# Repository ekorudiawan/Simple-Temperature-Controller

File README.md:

# Simple-Temperature-Controller
Simple Temperature Controller

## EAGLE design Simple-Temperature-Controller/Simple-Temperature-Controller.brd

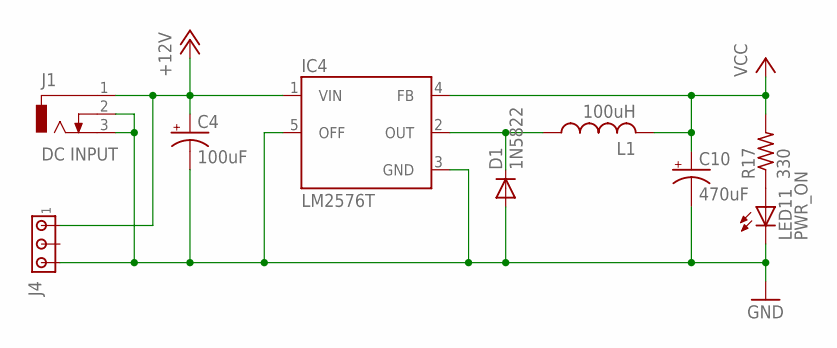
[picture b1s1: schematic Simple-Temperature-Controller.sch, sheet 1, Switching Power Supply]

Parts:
C4: 100uF; E2,5-6
C10: 470uF; E3,5-8
D1: 1N5822; DO201-15
IC4: LM2576T; TO220-5
J1: DC INPUT; DCJ0202
J4: MTA03-100; 10X03MTA
L1: 100uH; TJ3-U2
LED11: PWR_ON; LED3MM
R17: 330; 0207/10

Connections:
+12V: C4.+, IC4.1 (VIN), J1.1, J4.1; also elsewhere on the board
GND: C4.-, C10.-, D1.A, IC4.3 (GND), IC4.5 (OFF), J1.2, J1.3, J4.3, LED11.K (C); also elsewhere on the board
unnamed: D1.C, IC4.2 (OUT), L1.1
unnamed: LED11.A, R17.1
VCC: C10.+, IC4.4 (FB), L1.2, R17.2; also elsewhere on the board

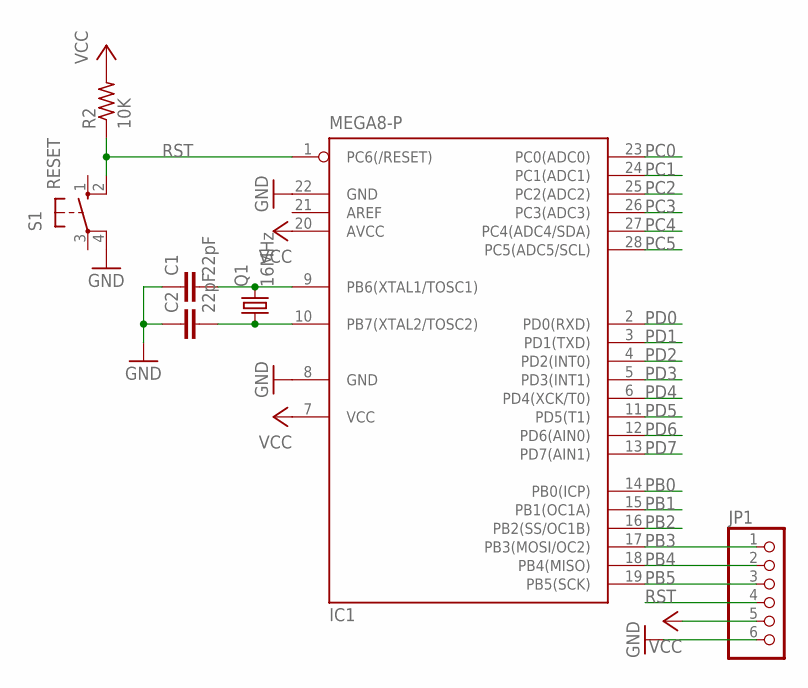
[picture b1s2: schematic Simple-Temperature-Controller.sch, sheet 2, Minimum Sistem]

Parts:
C1, C2: 22pF; RESISTOR_C025-024X044
IC1: MEGA8-P; DIL28-3
JP1: PINHD-1X6; 1X06
Q1: 16MHz; HC49/S
R2: 10K; RESISTOR_0207/10
S1: RESET; B3F-10XX

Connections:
GND: C1.1, C2.1, IC1.8 (GND), IC1.22 (GND), JP1.6, S1.4 (P1); also elsewhere on the board
unnamed: C1.2, IC1.9 (PB6(XTAL1/TOSC1)), Q1.2
unnamed: C2.2, IC1.10 (PB7(XTAL2/TOSC2)), Q1.1
PB0: IC1.14 (PB0(ICP)); also elsewhere on the board
PB1: IC1.15 (PB1(OC1A)); also elsewhere on the board
PB2: IC1.16 (PB2(SS/OC1B)); also elsewhere on the board
PB3: IC1.17 (PB3(MOSI/OC2)), JP1.1; also elsewhere on the board
PB4: IC1.18 (PB4(MISO)), JP1.2; also elsewhere on the board
PB5: IC1.19 (PB5(SCK)), JP1.3; also elsewhere on the board
PC0: IC1.23 (PC0(ADC0)); also elsewhere on the board
PC1: IC1.24 (PC1(ADC1)); also elsewhere on the board
PC2: IC1.25 (PC2(ADC2)); also elsewhere on the board
PC3: IC1.26 (PC3(ADC3)); also elsewhere on the board
PC4: IC1.27 (PC4(ADC4/SDA)); also elsewhere on the board
PC5: IC1.28 (PC5(ADC5/SCL)); also elsewhere on the board
PD0: IC1.2 (PD0(RXD)); also elsewhere on the board
PD1: IC1.3 (PD1(TXD)); also elsewhere on the board
PD2: IC1.4 (PD2(INT0)); also elsewhere on the board
PD3: IC1.5 (PD3(INT1)); also elsewhere on the board
PD4: IC1.6 (PD4(XCK/T0)); also elsewhere on the board
PD5: IC1.11 (PD5(T1))
PD6: IC1.12 (PD6(AIN0))
PD7: IC1.13 (PD7(AIN1))
RST: IC1.1 (PC6(/RESET)), JP1.4, R2.1, S1.2 (S1)
VCC: IC1.7 (VCC), IC1.20 (AVCC), JP1.5, R2.2; also elsewhere on the board

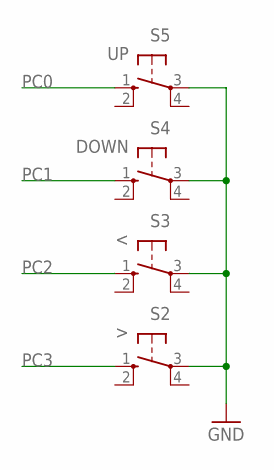
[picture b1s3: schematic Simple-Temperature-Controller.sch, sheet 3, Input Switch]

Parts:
S2: >; B3F-10XX; MPN B3F-1000
S3: <; B3F-10XX; MPN B3F-1000
S4: DOWN; B3F-10XX; MPN B3F-1000
S5: UP; B3F-10XX; MPN B3F-1000

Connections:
GND: S2.3, S3.3, S4.3, S5.3; also elsewhere on the board
PC0: S5.1 (S); also elsewhere on the board
PC1: S4.1 (S); also elsewhere on the board
PC2: S3.1 (S); also elsewhere on the board
PC3: S2.1 (S); also elsewhere on the board

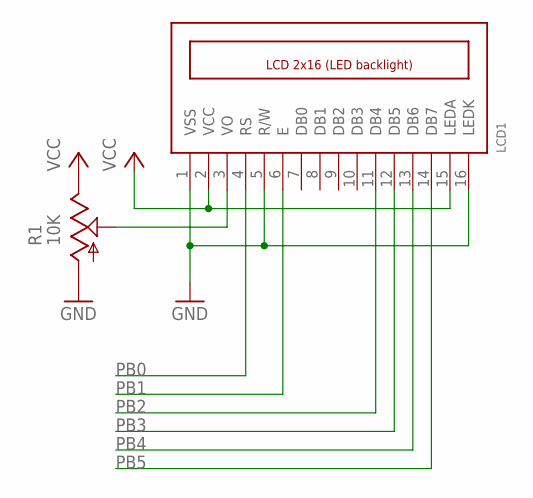
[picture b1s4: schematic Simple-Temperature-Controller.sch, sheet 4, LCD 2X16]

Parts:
LCD1: LCD-2X16
R1: 10K; POT_CA6V

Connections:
GND: LCD1.1 (VSS), LCD1.5 (R/W), LCD1.16 (LEDK), R1.A; also elsewhere on the board
unnamed: LCD1.3 (VO), R1.S
PB0: LCD1.4 (RS); also elsewhere on the board
PB1: LCD1.6 (E); also elsewhere on the board
PB2: LCD1.11 (DB4); also elsewhere on the board
PB3: LCD1.12 (DB5); also elsewhere on the board
PB4: LCD1.13 (DB6); also elsewhere on the board
PB5: LCD1.14 (DB7); also elsewhere on the board
VCC: LCD1.2 (VCC), LCD1.15 (LEDA), R1.E; also elsewhere on the board

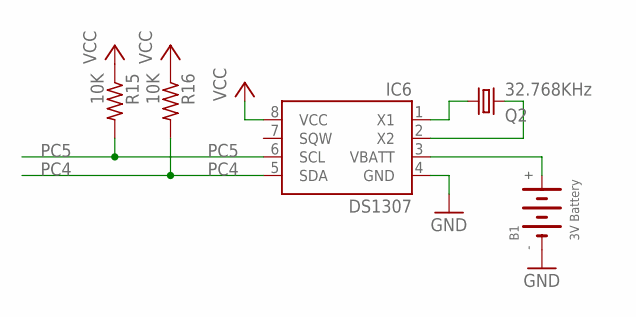
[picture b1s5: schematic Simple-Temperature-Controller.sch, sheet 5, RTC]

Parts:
B1: 3V Battery; CR2032
IC6: DS1307; DIP08
Q2: 32.768KHz; TC26H
R15, R16: 10K; 0207/10

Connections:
GND: B1.-, IC6.4 (GND); also elsewhere on the board
unnamed: IC6.1 (X1), Q2.1
unnamed: IC6.2 (X2), Q2.2
unnamed: B1.+, IC6.3 (VBATT)
PC4: IC6.5 (SDA), R16.2; also elsewhere on the board
PC5: IC6.6 (SCL), R15.2; also elsewhere on the board
VCC: IC6.8 (VCC), R15.1, R16.1; also elsewhere on the board

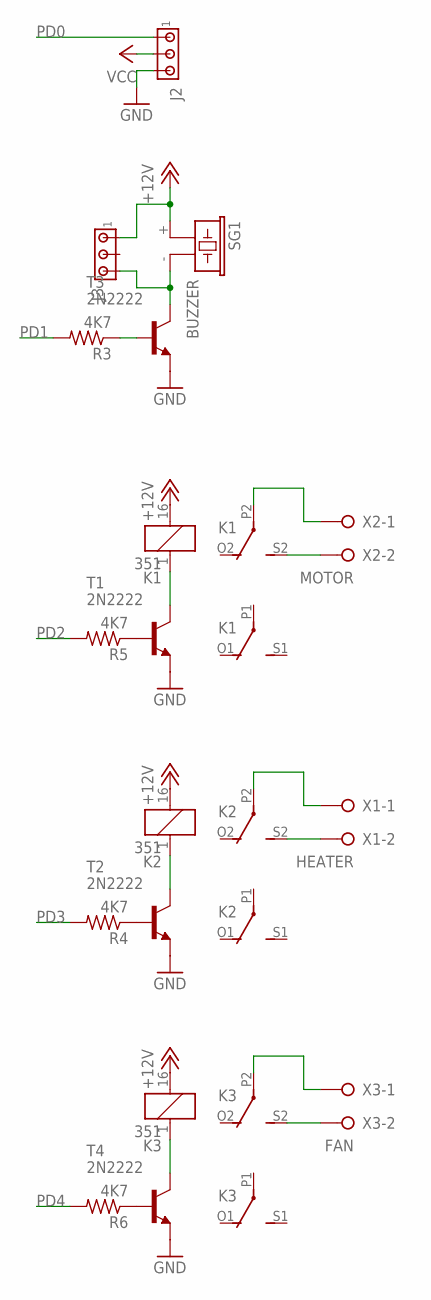
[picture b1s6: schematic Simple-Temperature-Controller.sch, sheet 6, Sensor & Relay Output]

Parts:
J2, J3: MTA03-100; 10X03MTA
K1, K2, K3: 351
R3, R4, R5, R6: 4K7; 0207/10
SG1: BUZZER; F/CM12P
T1, T2, T3, T4: 2N2222; TO92-EBC-OVAL
X1: HEATER; W237-132
X2: MOTOR; W237-132
X3: FAN; W237-132

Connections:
+12V: J3.1, K1.16 (2), K2.16 (2), K3.16 (2), SG1.+ (1); also elsewhere on the board
GND: J2.3, T1.E, T2.E, T3.E, T4.E; also elsewhere on the board
unnamed: R5.1, T1.B
unnamed: K1.1, T1.C
unnamed: K2.1, T2.C
unnamed: K1.P2, X2.1
unnamed: K2.S2 (S), X1.2
unnamed: R4.1, T2.B
unnamed: K3.1, T4.C
unnamed: K3.S2 (S), X3.2
unnamed: R6.1, T4.B
unnamed: K1.S2 (S), X2.2
unnamed: K2.P2, X1.1
unnamed: K3.P2, X3.1
unnamed: J3.3, SG1.- (2), T3.C
unnamed: R3.1, T3.B
PD0: J2.1; also elsewhere on the board
PD1: R3.2; also elsewhere on the board
PD2: R5.2; also elsewhere on the board
PD3: R4.2; also elsewhere on the board
PD4: R6.2; also elsewhere on the board
VCC: J2.2; also elsewhere on the board

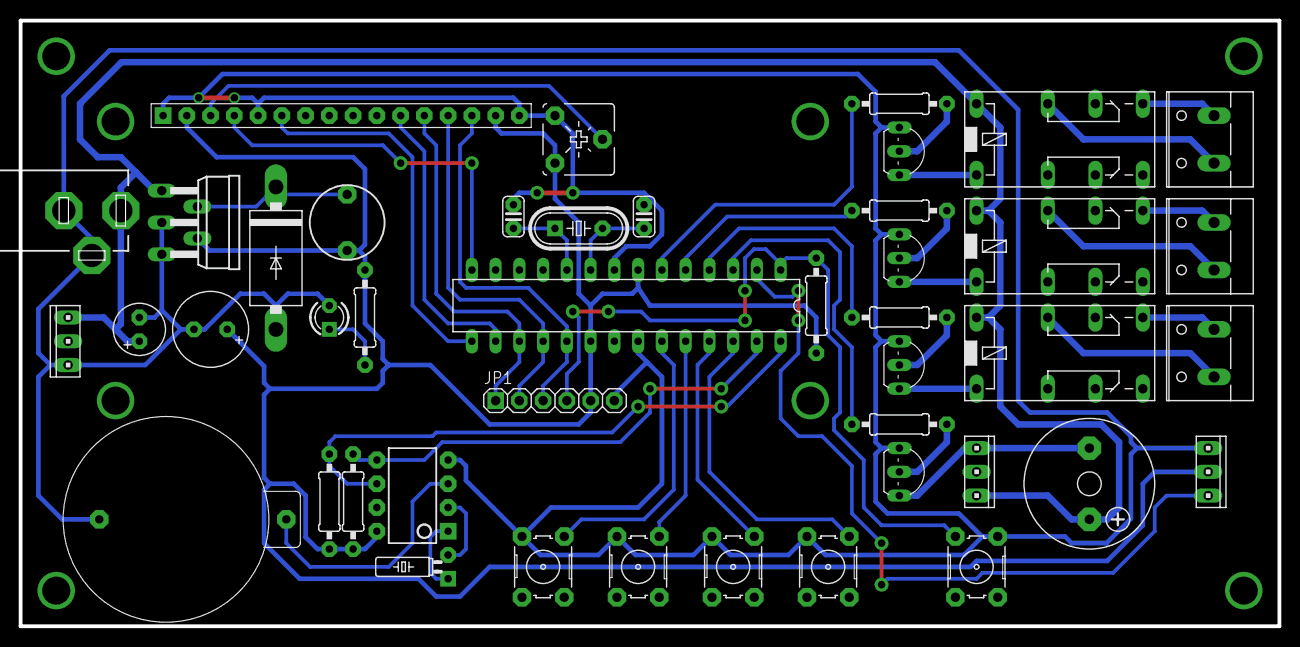
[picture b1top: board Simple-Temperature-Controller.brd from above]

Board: 2 copper layers, 134.6 x 64.8 mm, 44 parts (0 on the bottom side), 43 nets.

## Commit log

2017-10-03 Added source files
